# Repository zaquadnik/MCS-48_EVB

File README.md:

# MCS-48_EVB

Simple computer system using MCS-48 family microcontroller. System contains external program memory & external data memory. The external data memory uses the 62256 (32k x 8b) SRAM memory. The microcontroller directly addresses the 256 bytes of the memory, but the system adds the possibility of bank switching using the 8243 GPIO expander. The bank switching is done in software. It can be leveraged to implement multi-tasking environment with hard task memory separation. The external data memory contains 128 banks, 256 bytes each.
The external program memory uses 8k x 8b 27C64 EPROM memory. The microcontroller max program memory size is 4kB, thus EPROM contain two 4kB banks, that can be switched using the 8243 expander. This feature is experimental, thus HW jumper is added that enables setting the EPROM's A12 line to logical '0' by connecting it to the ground.

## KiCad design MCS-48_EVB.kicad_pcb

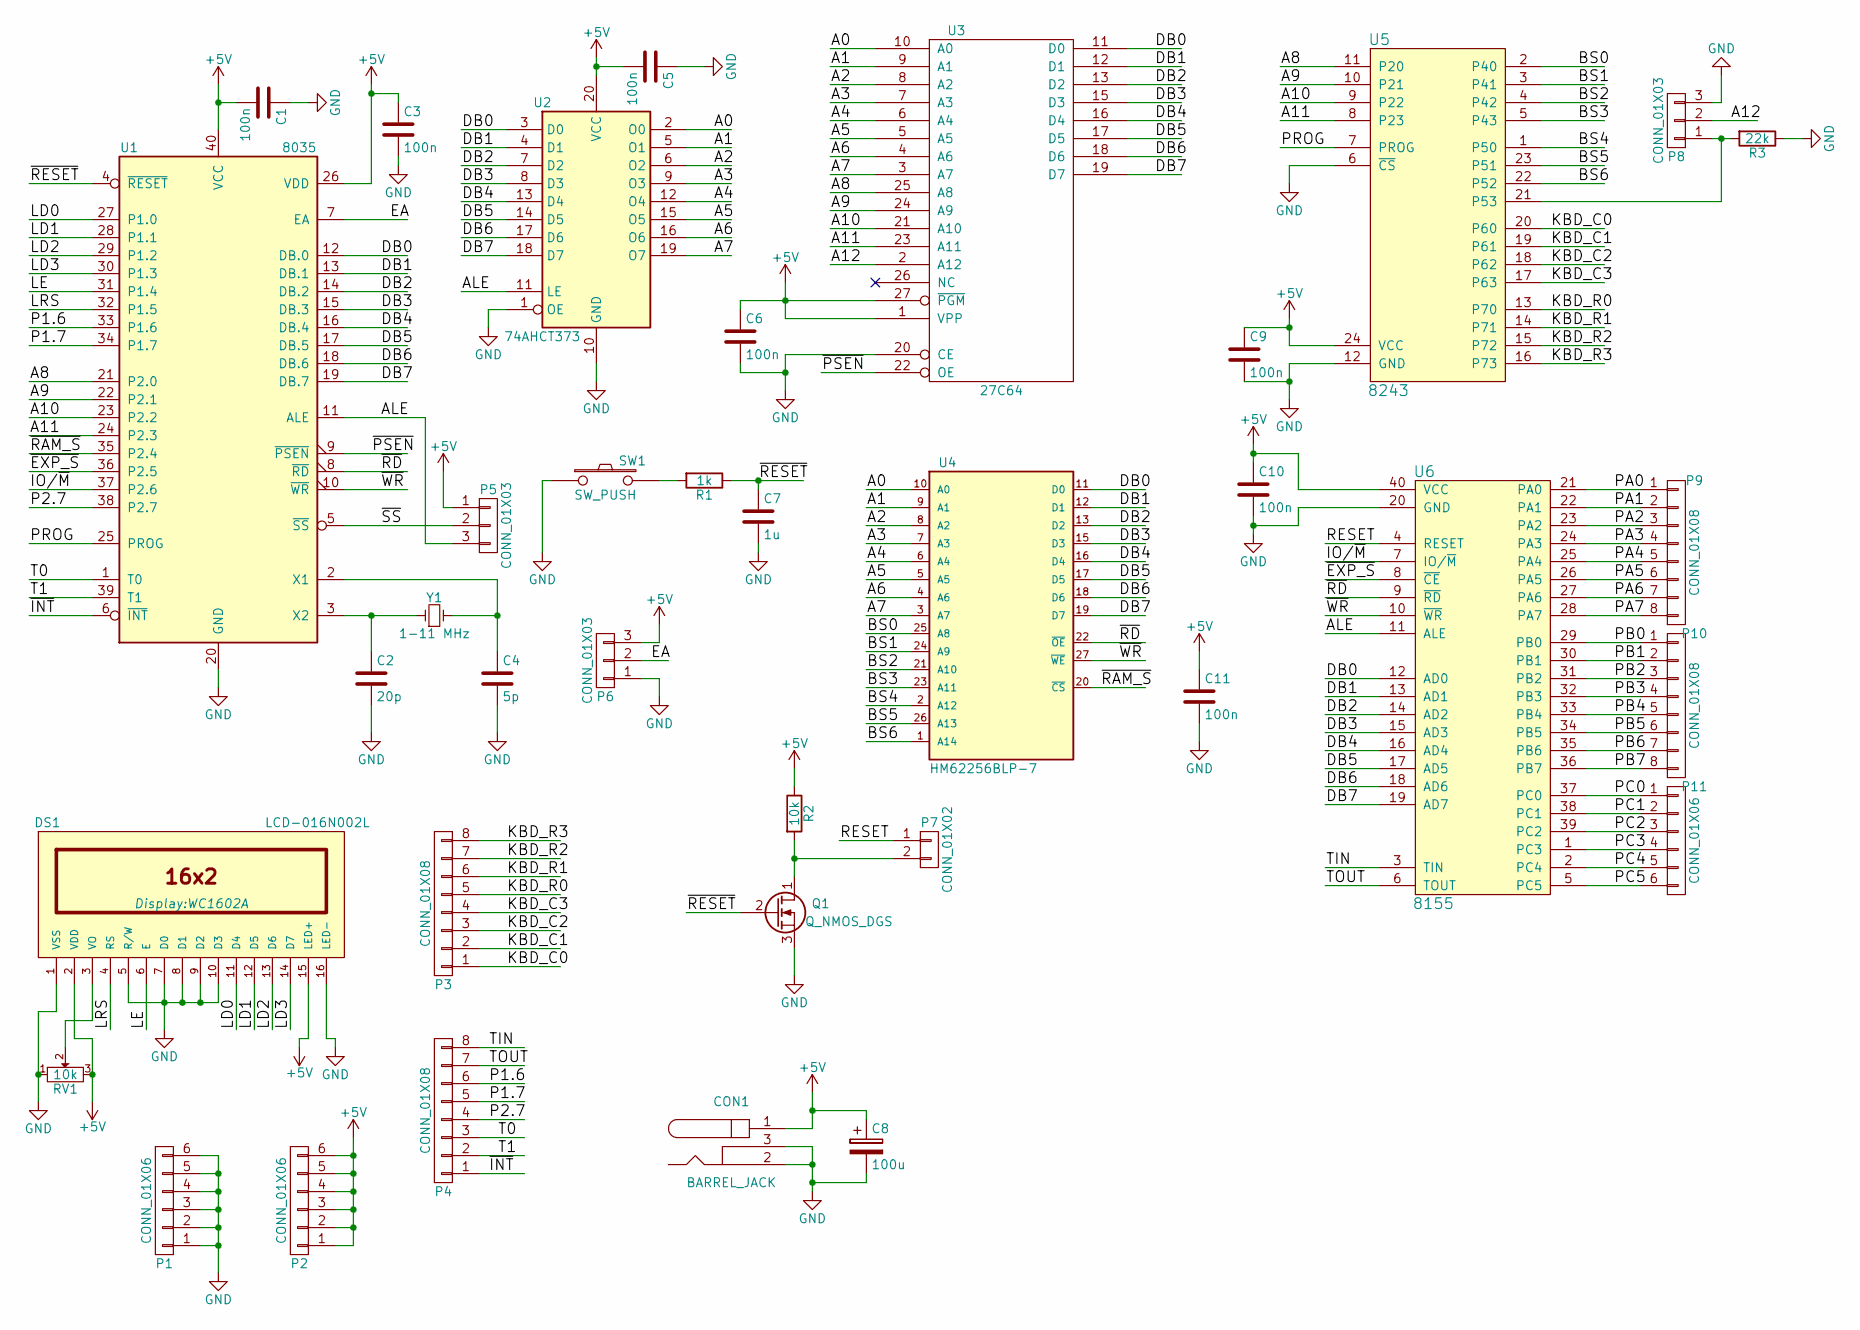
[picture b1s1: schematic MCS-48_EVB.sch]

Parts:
C1, C3, C5, C6, C9, C10, C11: 100n; C_0805_HandSoldering
C2: 20p; C_0805_HandSoldering
C4: 5p; C_0805_HandSoldering
C7: 1u; C_0805_HandSoldering
C8: 100u; CP_Radial_D6.3mm_P2.50mm
CON1: BARREL_JACK
DS1: LCD-016N002L; WC1602A
P1, P2, P11: CONN_01X06; Pin_Header_Straight_1x06_Pitch2.54mm
P3, P4, P9, P10: CONN_01X08; Pin_Header_Straight_1x08_Pitch2.54mm
P5, P6, P8: CONN_01X03; Pin_Header_Straight_1x03_Pitch2.54mm
P7: CONN_01X02; Pin_Header_Straight_1x02_Pitch2.54mm
Q1: Q_NMOS_DGS; TO-92_Inline_Narrow_Oval
R1: 1k; R_0805_HandSoldering
R2: 10k; R_0805_HandSoldering
R3: 22k; R_0805_HandSoldering
RV1: 10k; Potentiometer_Trimmer_ACP_CA9v_Horizontal_Px10.0mm_Py5.0mm
SW1: SW_PUSH; SW_PUSH_6mm
U1: 8035; DIP-40_W15.24mm_LongPads
U2: 74AHCT373; DIP-20_W7.62mm_LongPads
U3: 27C64; DIP-28_W15.24mm_LongPads
U4: HM62256BLP-7; DIP-28_W15.24mm_LongPads
U5: 8243; DIP-24_W15.24mm_LongPads
U6: 8155; DIP-40_W15.24mm_LongPads
Y1: 1-11 MHz; Crystal_HC18-U_Vertical

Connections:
+5V: C1.2, C3.1, C5.2, C6.1, C8.1, C9.1, C10.1, C11.1, CON1.1, DS1.2 (VDD), DS1.15 (LED+), P2.1, P2.2, P2.3, P2.4, P2.5, P2.6, P5.1, P6.3, R2.1, RV1.3, U1.26 (VDD), U1.40 (VCC), U2.20 (VCC), U3.1 (VPP), U3.27 (~PGM), U3.28 (VCC), U4.28 (VCC), U5.24 (VCC), U6.40 (VCC)
/A0: U2.2 (O0), U3.10 (A0), U4.10 (A0)
/A1: U2.5 (O1), U3.9 (A1), U4.9 (A1)
/A2: U2.6 (O2), U3.8 (A2), U4.8 (A2)
/A3: U2.9 (O3), U3.7 (A3), U4.7 (A3)
/A4: U2.12 (O4), U3.6 (A4), U4.6 (A4)
/A5: U2.15 (O5), U3.5 (A5), U4.5 (A5)
/A6: U2.16 (O6), U3.4 (A6), U4.4 (A6)
/A7: U2.19 (O7), U3.3 (A7), U4.3 (A7)
/A8: U1.21 (P2.0), U3.25 (A8), U5.11 (P20)
/A9: U1.22 (P2.1), U3.24 (A9), U5.10 (P21)
/A10: U1.23 (P2.2), U3.21 (A10), U5.9 (P22)
/A11: U1.24 (P2.3), U3.23 (A11), U5.8 (P23)
/A12: P8.2, U3.2 (A12)
/ALE: P5.3, U1.11 (ALE), U2.11 (LE), U6.11 (ALE)
/BS0: U4.25 (A8), U5.2 (P40)
/BS1: U4.24 (A9), U5.3 (P41)
/BS2: U4.21 (A10), U5.4 (P42)
/BS3: U4.23 (A11), U5.5 (P43)
/BS4: U4.2 (A12), U5.1 (P50)
/BS5: U4.26 (A13), U5.23 (P51)
/BS6: U4.1 (A14), U5.22 (P52)
/DB0: U1.12 (DB.0), U2.3 (D0), U3.11 (D0), U4.11 (D0), U6.12 (AD0)
/DB1: U1.13 (DB.1), U2.4 (D1), U3.12 (D1), U4.12 (D1), U6.13 (AD1)
/DB2: U1.14 (DB.2), U2.7 (D2), U3.13 (D2), U4.13 (D2), U6.14 (AD2)
/DB3: U1.15 (DB.3), U2.8 (D3), U3.15 (D3), U4.15 (D3), U6.15 (AD3)
/DB4: U1.16 (DB.4), U2.13 (D4), U3.16 (D4), U4.16 (D4), U6.16 (AD4)
/DB5: U1.17 (DB.5), U2.14 (D5), U3.17 (D5), U4.17 (D5), U6.17 (AD5)
/DB6: U1.18 (DB.6), U2.17 (D6), U3.18 (D6), U4.18 (D6), U6.18 (AD6)
/DB7: U1.19 (DB.7), U2.18 (D7), U3.19 (D7), U4.19 (D7), U6.19 (AD7)
/EA: P6.2, U1.7 (EA)
/IO/~M: U1.37 (P2.6), U6.7 (IO/~M)
/KBD_C0: P3.1, U5.20 (P60)
/KBD_C1: P3.2, U5.19 (P61)
/KBD_C2: P3.3, U5.18 (P62)
/KBD_C3: P3.4, U5.17 (P63)
/KBD_R0: P3.5, U5.13 (P70)
/KBD_R1: P3.6, U5.14 (P71)
/KBD_R2: P3.7, U5.15 (P72)
/KBD_R3: P3.8, U5.16 (P73)
/LD0: DS1.11 (D4), U1.27 (P1.0)
/LD1: DS1.12 (D5), U1.28 (P1.1)
/LD2: DS1.13 (D6), U1.29 (P1.2)
/LD3: DS1.14 (D7), U1.30 (P1.3)
/LE: DS1.6 (E), U1.31 (P1.4)
/LRS: DS1.4 (RS), U1.32 (P1.5)
/P1.6: P4.6, U1.33 (P1.6)
/P1.7: P4.5, U1.34 (P1.7)
/P2.7: P4.4, U1.38 (P2.7)
/PA0: P9.1, U6.21 (PA0)
/PA1: P9.2, U6.22 (PA1)
/PA2: P9.3, U6.23 (PA2)
/PA3: P9.4, U6.24 (PA3)
/PA4: P9.5, U6.25 (PA4)
/PA5: P9.6, U6.26 (PA5)
/PA6: P9.7, U6.27 (PA6)
/PA7: P9.8, U6.28 (PA7)
/PB0: P10.1, U6.29 (PB0)
/PB1: P10.2, U6.30 (PB1)
/PB2: P10.3, U6.31 (PB2)
/PB3: P10.4, U6.32 (PB3)
/PB4: P10.5, U6.33 (PB4)
/PB5: P10.6, U6.34 (PB5)
/PB6: P10.7, U6.35 (PB6)
/PB7: P10.8, U6.36 (PB7)
/PC0: P11.1, U6.37 (PC0)
/PC1: P11.2, U6.38 (PC1)
/PC2: P11.3, U6.39 (PC2)
/PC3: P11.4, U6.1 (PC3)
/PC4: P11.5, U6.2 (PC4)
/PC5: P11.6, U6.5 (PC5)
/PROG: U1.25 (PROG), U5.7 (PROG)
/RESET: P7.1, U6.4 (RESET)
/T0: P4.3, U1.1 (T0)
/T1: P4.2, U1.39 (T1)
/TIN: P4.8, U6.3 (TIN)
/TOUT: P4.7, U6.6 (TOUT)
/~EXP_S: U1.36 (P2.5), U6.8 (~CE)
/~INT: P4.1, U1.6 (~INT~)
/~PSEN: U1.9 (~PSEN~), U3.22 (OE)
/~RAM_S: U1.35 (P2.4), U4.20 (~CS)
/~RD: U1.8 (~RD~), U4.22 (~OE), U6.9 (~RD)
/~RESET: C7.1, Q1.2 (G), R1.1, U1.4 (~RESET~)
/~SS: P5.2, U1.5 (~SS~)
/~WR: U1.10 (~WR~), U4.27 (~WE), U6.10 (~WR)
GND: C1.1, C2.2, C3.2, C4.2, C5.1, C6.2, C7.2, C8.2, C9.2, C10.2, C11.2, CON1.2, CON1.3, DS1.1 (VSS), DS1.5 (R/W), DS1.7 (D0), DS1.8 (D1), DS1.9 (D2), DS1.10 (D3), DS1.16 (LED-), P1.1, P1.2, P1.3, P1.4, P1.5, P1.6, P6.1, P8.3, Q1.3 (S), R3.1, RV1.1, SW1.1, U1.20 (GND), U2.1 (OE), U2.10 (GND), U3.14 (GND), U3.20 (CE), U4.14 (GND), U5.6 (~CS), U5.12 (GND), U6.20 (GND)
unnamed: C2.1, U1.3 (X2), Y1.1
unnamed: C4.1, U1.2 (X1), Y1.2
unnamed: DS1.3 (VO), RV1.2
unnamed: P7.2, Q1.1 (D), R2.2
unnamed: P8.1, R3.2, U5.21 (P53)
unnamed: R1.2, SW1.2

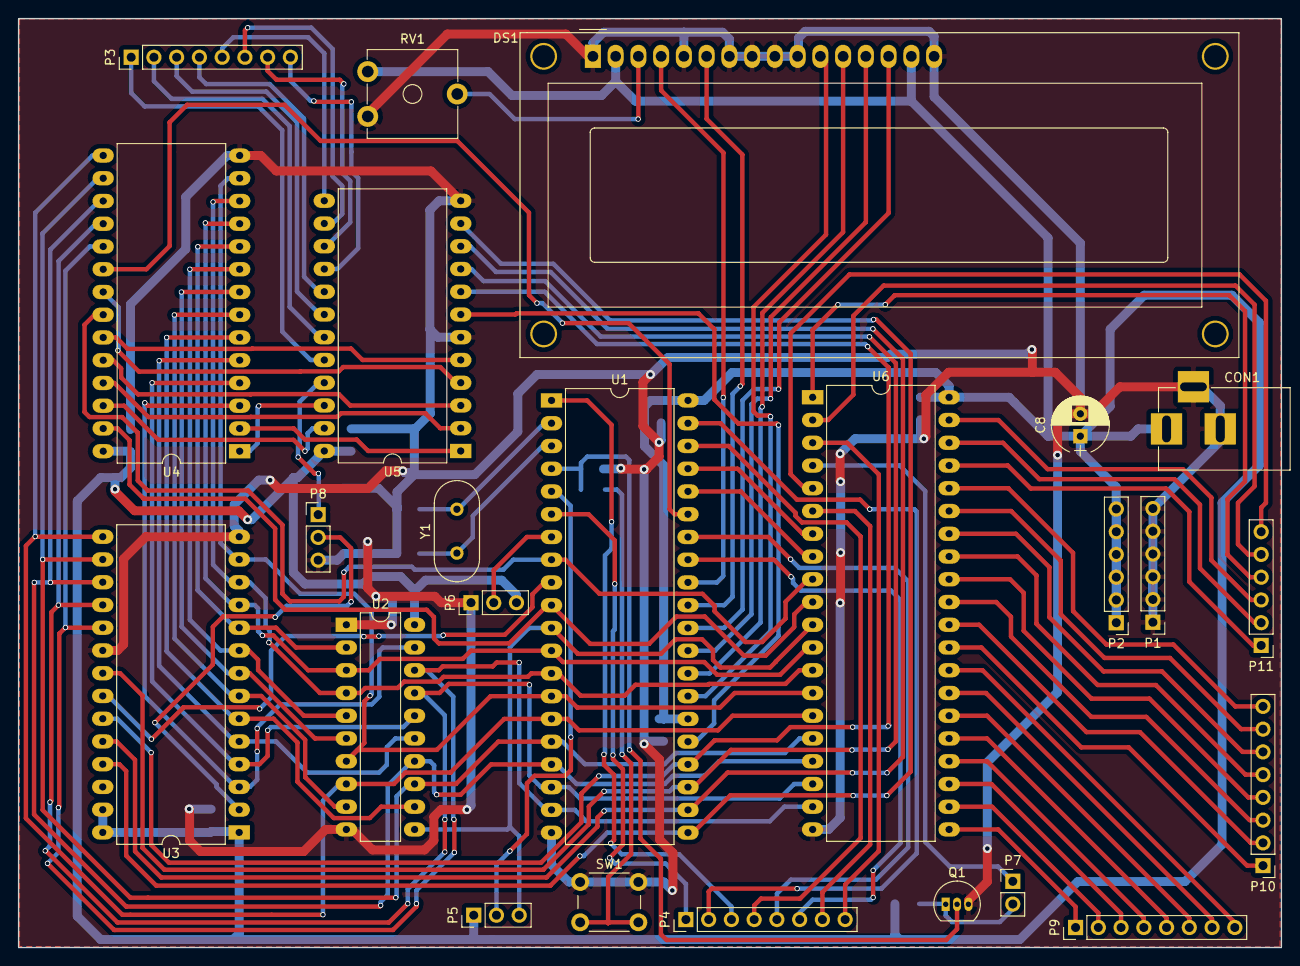
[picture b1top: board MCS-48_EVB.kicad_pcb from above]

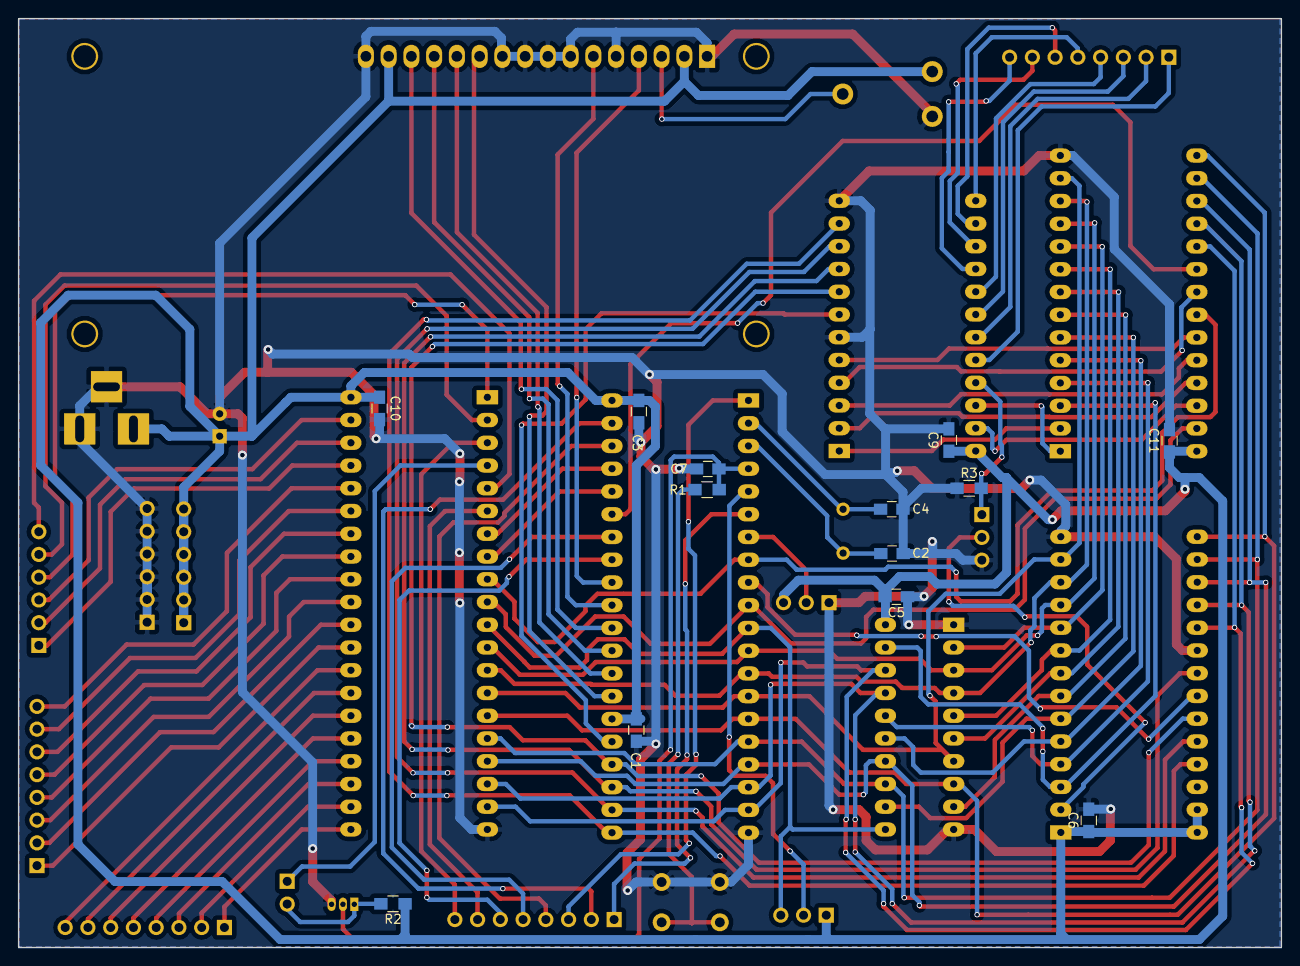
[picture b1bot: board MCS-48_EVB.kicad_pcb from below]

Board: 2 copper layers, 141.0 x 103.7 mm, 37 parts (13 on the bottom side), 92 nets.

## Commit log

2023-01-03 Started working on schematic.
2023-01-06 Added memories & expander
2023-01-06 Added RESET and EA circuits. Added MCS-48 docs.
2023-01-06 Added IC footprints
2023-01-06 Added separate library.
2023-01-07 Added 8155 expander
2023-01-07 Added LCD & keyb conn
2023-01-07 Added connectors. Power connector and step mode circuit left.
2023-01-08 Started working on PCB.
2023-01-09 Working on component placement
2023-01-09 Finished component placement.
2023-01-09 Added board outline.
2023-01-15 Working on spaghetti-tracing
2023-01-15 Working on spaghetti-tracing. Only GND left.
2023-01-15 All nets connected
2023-01-15 Added GND planes
2023-01-15 Generated gerber files
2023-01-25 Corrected gerber files
